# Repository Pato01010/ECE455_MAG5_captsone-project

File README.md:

# AfriCAN DETECT IT: Proton-Precession Magnetometer

This project is a towed underwater magnetometer for marine magnetic surveying and object recovery. It's dragged behind a boat and maps small changes in Earth's magnetic field, the kind made by shipwrecks, debris, and other metal objects on or under the seafloor.

The goal is a low-cost instrument with **sub-1 nT sensitivity**, every reading tagged with **GPS position**, and everything packed into a **waterproof towfish** that works in the field.

## How it works

The system is a proton-precession magnetometer (PPM). A coil is wrapped around a container of hydrogen-rich fluid, such as water or kerosene.

1. **Polarize.** A large DC current through the coil sets up a strong field that lines up the proton spins in the fluid.
2. **Release.** The current is cut quickly. The protons start to precess around Earth's field.
3. **Sense.** The precessing protons induce a weak signal in the same coil, in the microvolt range and decaying over a few seconds.
4. **Measure.** The precession frequency is directly proportional to field strength (about 42.58 Hz per µT, which is roughly 2 kHz in Earth's field). Counting that frequency precisely gives an absolute field reading.
5. **Log.** Each reading is timestamped and paired with a GPS fix, so a survey becomes a map of the magnetic field.

The method is attractive because the measurement comes from a physical constant, the proton's gyromagnetic ratio. It doesn't drift and needs no calibration. The hard part is pulling a tiny, decaying signal out of noise right after a high-current pulse.

## System design

```
 ┌────────────┐   ┌──────────┐   ┌──────────────┐   ┌──────────────┐   ┌─────────┐
 │Polarization│──▶│ Sensor   │──▶│ Blanking +   │──▶│ Filtering &  │──▶│   MCU   │
 │  driver    │   │  coil    │   │   preamp     │   │    gain      │   │ freq.   │
 └────────────┘   └──────────┘   └──────────────┘   └──────────────┘   │ counter │
                                                                       └────┬────┘
                                                          GPS ─────────────▶│
                                                                            ▼
                                                                    Logged survey data
```

| Subsystem                       | Role                                                                                                                   |
| ------------------------------- | ---------------------------------------------------------------------------------------------------------------------- |
| **Polarization driver**   | Switches high current into the coil, then shuts it off fast and cleanly                                                |
| **Sensor coil**           | Polarizes the fluid, then picks up the precession signal                                                               |
| **Blanking + preamp**     | Shields the sensitive front end during turn-off, then amplifies the weak signal with as little added noise as possible |
| **Signal conditioning**   | Band-pass filtering and gain centered on the expected precession frequency                                             |
| **Frequency measurement** | MCU-based period counting for precise frequency estimates over a short, decaying signal                                |
| **GPS integration**       | Position and timing for every reading                                                                                  |
| **Isolation**             | Keeps switching noise and ground currents from the power side out of the analog chain                                  |
| **Towfish housing**       | Waterproof, non-magnetic enclosure that keeps the sensor stable and away from the boat's own magnetic signature        |

## Our approach

We're building this as a set of independent subsystems. Each one is designed, built, and tested on its own before integration. That lets us confirm each stage works and track down problems without guessing which part of the chain is at fault.

**1. Design for the signal.** The precession signal is tiny and short-lived, so every design choice starts from the noise budget: coil geometry and wire, preamp noise, filter bandwidth, and how fast the front end can recover after the polarizing pulse.

**2. Prototype and test on the bench.** Each subsystem gets its own custom PCB and bench test. We check polarization switching, front-end blanking and gain, coil pickup, and frequency and GPS logging separately against known inputs.

**3. Fight noise and ringing.** The biggest challenges are coil ringing after turn-off, environmental and switching noise, and weak-signal recovery. We handle these with fast, well-damped switching, careful blanking, narrow filtering, shielding, and isolating the high-current side from the analog side.

**4. Integrate in stages.** Subsystems are combined one at a time, and we confirm performance at each step before adding the next.

**5. Package and field test.** The finished electronics go into the towfish. We test it in the water, first over open water and then over known magnetic targets, to verify sensitivity and positioning in real survey conditions.

## Repo layout

```
hardware/     Schematics and PCB layouts for each subsystem
firmware/     MCU code for timing, frequency measurement, and GPS logging
analysis/     Scripts for processing survey data and making field maps
mechanical/   Towfish housing design files
docs/         Design notes, test results, and bring-up procedures
```

## Safety

The polarization stage switches high current into an inductive load. Read the bring-up notes in `docs/` before powering the hardware, and confirm the blanking and flyback paths are in place first.

## Team

**AfriCAN DETECT IT**, Electrical & Computer Engineering, University of Wisconsin–Madison.

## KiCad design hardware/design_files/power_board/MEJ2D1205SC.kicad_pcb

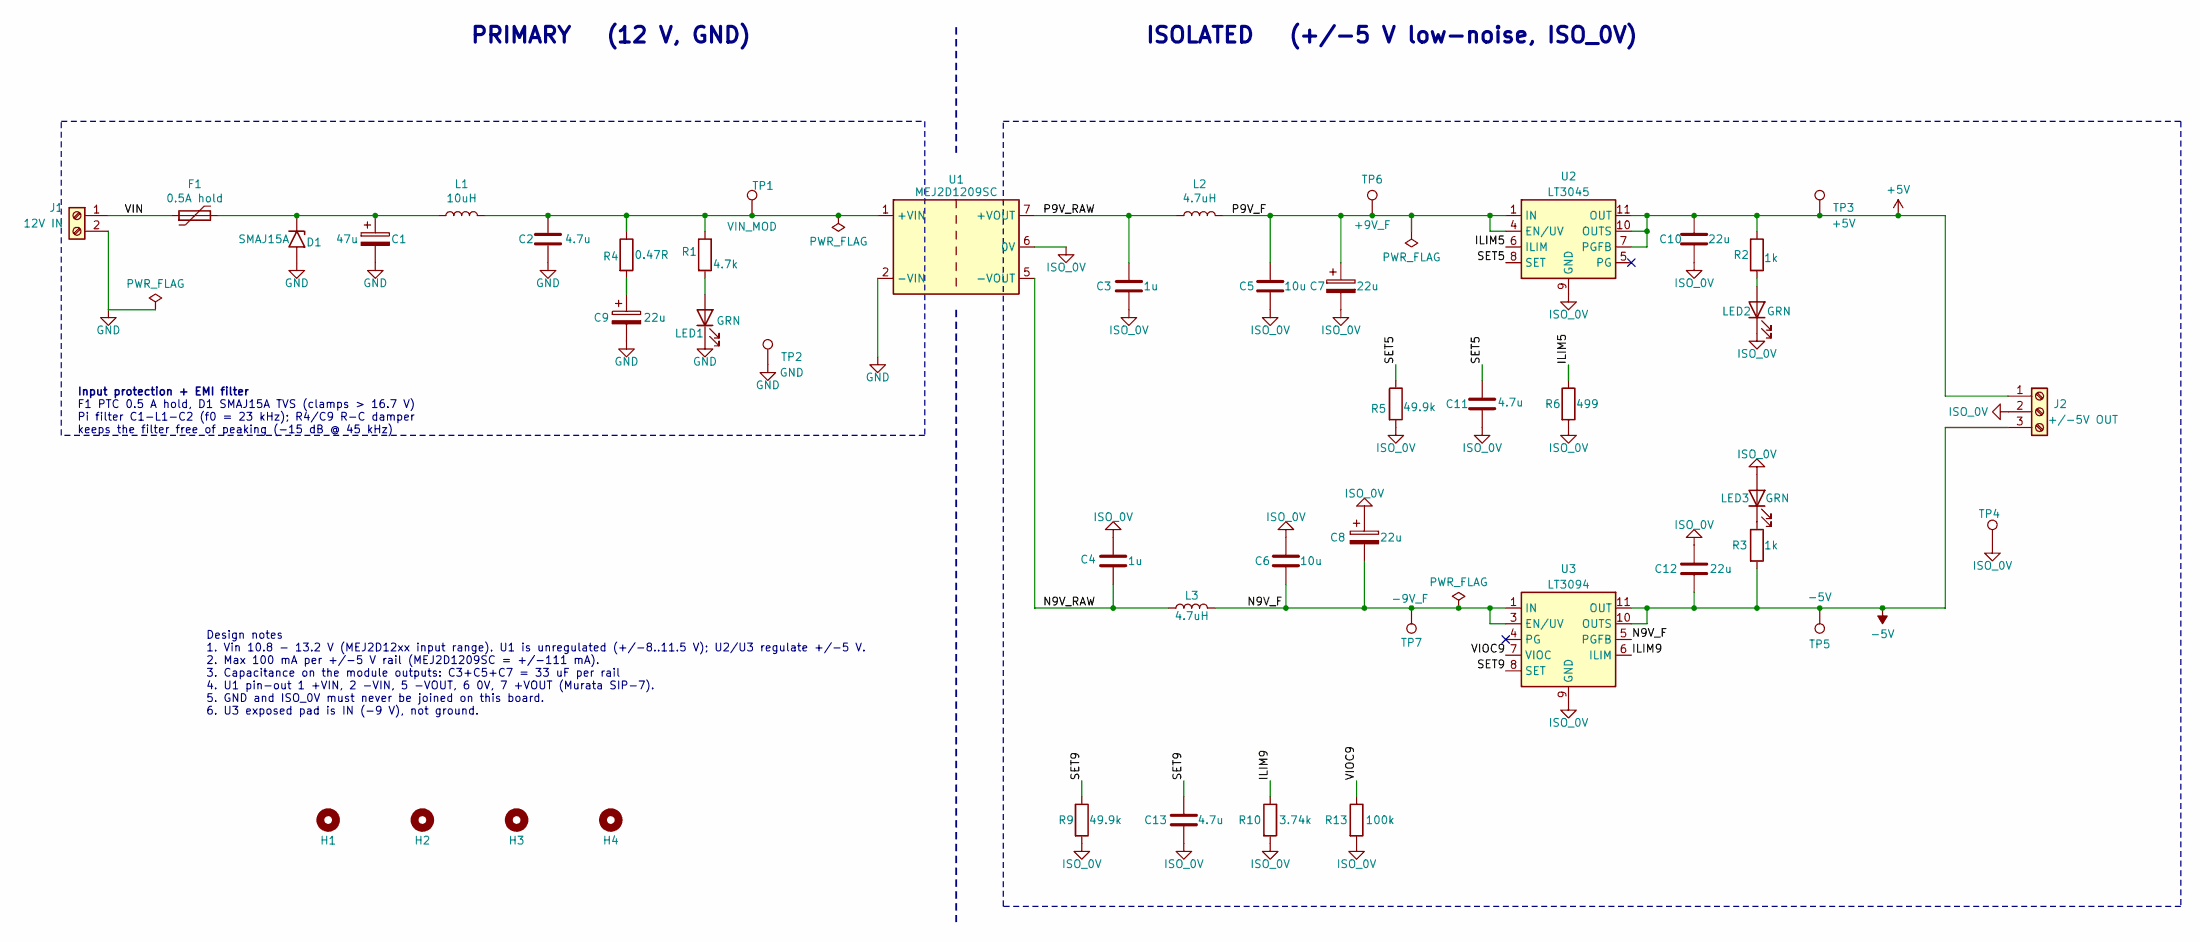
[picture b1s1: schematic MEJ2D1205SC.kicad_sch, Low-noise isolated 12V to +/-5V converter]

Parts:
C1: 47u; CP_Elec_6.3x7.7; MPN Panasonic EEE-FK1E470P
C2: 4.7u; C_1206_3216Metric; MPN Murata GRM31CR71E475KA88
C3, C4: 1u; C_0805_2012Metric; MPN Murata GRM21BR71C105KA01L
C5, C6: 10u; C_1206_3216Metric; MPN Murata GRM31CR71E106KA12L
C7, C8, C9: 22u; CP_Elec_5x5.8; MPN Panasonic EEE-FK1E220R
C10, C12: 22u; C_1210_3225Metric; MPN Murata GRM32ER71C226KE18L
C11, C13: 4.7u; C_1206_3216Metric; MPN Murata GRM31CR71C475KA01L
D1: SMAJ15A; D_SMA; MPN Littelfuse SMAJ15A
F1: 0.5A hold; Fuse_1206_3216Metric; MPN Littelfuse 1206L050/15YR
H1, H2, H3, H4: M3; MountingHole_3.2mm_M3
J1: 12V IN; TerminalBlock_Phoenix_MKDS-1,5-2-5.08_1x02_P5.08mm_Horizont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; MPN Phoenix Contact 1729128
J2: +/-5V OUT; TerminalBlock_Phoenix_MKDS-1,5-3-5.08_1x03_P5.08mm_Horizont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; MPN Phoenix Contact 1729131
L1: 10uH; L_Bourns-SRN4018; MPN Bourns SRN4018-100M
L2, L3: 4.7uH; L_Bourns-SRN4018; MPN Bourns SRN4018-4R7M
LED1, LED2, LED3: GRN; LED_0805_2012Metric; MPN Lite-On LTST-C171GKT
R1: 4.7k; R_0805_2012Metric; MPN Yageo RC0805FR-074K7L
R2, R3: 1k; R_0805_2012Metric; MPN Yageo RC0805FR-071KL
R4: 0.47R; R_0805_2012Metric; MPN Yageo RL0805FR-070R47L
R5, R9: 49.9k; R_0805_2012Metric; MPN Panasonic ERA-6AEB4992V
R6: 499; R_0805_2012Metric; MPN Yageo RC0805FR-07499RL
R10: 3.74k; R_0805_2012Metric; MPN Yageo RC0805FR-073K74L
R13: 100k; R_0805_2012Metric; MPN Yageo RC0805FR-07100KL
TP1: VIN_MOD; TestPoint_Keystone_5010-5014_Multipurpose; MPN Keystone 5010
TP2: GND; TestPoint_Keystone_5010-5014_Multipurpose; MPN Keystone 5011
TP3: +5V; TestPoint_Keystone_5010-5014_Multipurpose; MPN Keystone 5010
TP4: ISO_0V; TestPoint_Keystone_5010-5014_Multipurpose; MPN Keystone 5011
TP5: -5V; TestPoint_Keystone_5010-5014_Multipurpose; MPN Keystone 5010
TP6: +9V_F; TestPoint_Keystone_5010-5014_Multipurpose; MPN Keystone 5010
TP7: -9V_F; TestPoint_Keystone_5010-5014_Multipurpose; MPN Keystone 5010
U1: MEJ2D1209SC; Murata_MEJ2DxxxxSC_THT; MPN Murata MEJ2D1209SC
U2: LT3045; MSOP-12-1EP_3x4.039mm_P0.65mm_EP1.651x2.845mm; MPN Analog Devices LT3045EMSE#PBF
U3: LT3094; MSOP-12-1EP_3x4.039mm_P0.65mm_EP1.651x2.845mm; MPN Analog Devices LT3094EMSE#PBF

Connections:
+5V: C10.1, J2.1, R2.1, TP3.1 (1_1), U2.7 (PGFB), U2.10 (OUTS), U2.11 (OUT), U2.12 (OUT)
-5V: C12.2, J2.3, R3.2, TP5.1 (1_1), U3.10 (OUTS), U3.11 (OUT), U3.12 (OUT)
/ILIM5: R6.1, U2.6 (ILIM)
/ILIM9: R10.1, U3.6 (ILIM)
/N9V_F: C6.2, C8.2, L3.2, TP7.1 (1_1), U3.1 (IN), U3.2 (IN), U3.3 (EN/UV), U3.5 (PGFB), U3.13 (IN)
/N9V_RAW: C4.2, L3.1, U1.5 (-VOUT)
/P9V_F: C5.1, C7.1, L2.2, TP6.1 (1_1), U2.1 (IN), U2.2 (IN), U2.3 (IN), U2.4 (EN/UV)
/P9V_RAW: C3.1, L2.1, U1.7 (+VOUT)
/SET5: C11.1, R5.1, U2.8 (SET)
/SET9: C13.1, R9.1, U3.8 (SET)
/VIN: F1.1, J1.1
/VIOC9: R13.1, U3.7 (VIOC)
GND: C1.2, C2.2, C9.2, D1.2 (A), J1.2, LED1.1 (K), TP2.1 (1_1), U1.2 (-VIN)
ISO_0V: C3.2, C4.1, C5.2, C6.1, C7.2, C8.1, C10.2, C11.2, C12.1, C13.2, J2.2, LED2.1 (K), LED3.2 (A), R5.2, R6.2, R9.2, R10.2, R13.2, TP4.1 (1_1), U1.6 (0V), U2.9 (GND), U2.13 (GND), U3.9 (GND)
unnamed: C9.1, R4.2
unnamed: C1.1, D1.1 (K), F1.2, L1.1
unnamed: LED1.2 (A), R1.2
unnamed: LED2.2 (A), R2.2
unnamed: LED3.1 (K), R3.1
unnamed: C2.1, L1.2, R1.1, R4.1, TP1.1 (1_1), U1.1 (+VIN)

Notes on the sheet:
ISOLATED (+/-5 V low-noise, ISO_0V)
Design notes 1. Vin 10.8 - 13.2 V (MEJ2D12xx input range). U1 is unregulated (+/-8..11.5 V); U2/U3 regulate +/-5 V. 2. Max 100 mA per +/-5 V rail (MEJ2D1209SC = +/-111 mA). 3. Capacitance on the module outputs: C3+C5+C7 = 33 uF per rail 4. U1 pin-out 1 +VIN, 2 -VIN, 5 -VOUT, 6 0V, 7 +VOUT (Murata S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
F1 PTC 0.5 A hold, D1 SMAJ15A TVS (clamps > 16.7 V) Pi filter C1-L1-C2 (f0 = 23 kHz); R4/C9 R-C damper keeps the filter free of peaking (-15 dB @ 45 kHz)
PRIMARY (12 V, GND)
Input protection + EMI filter

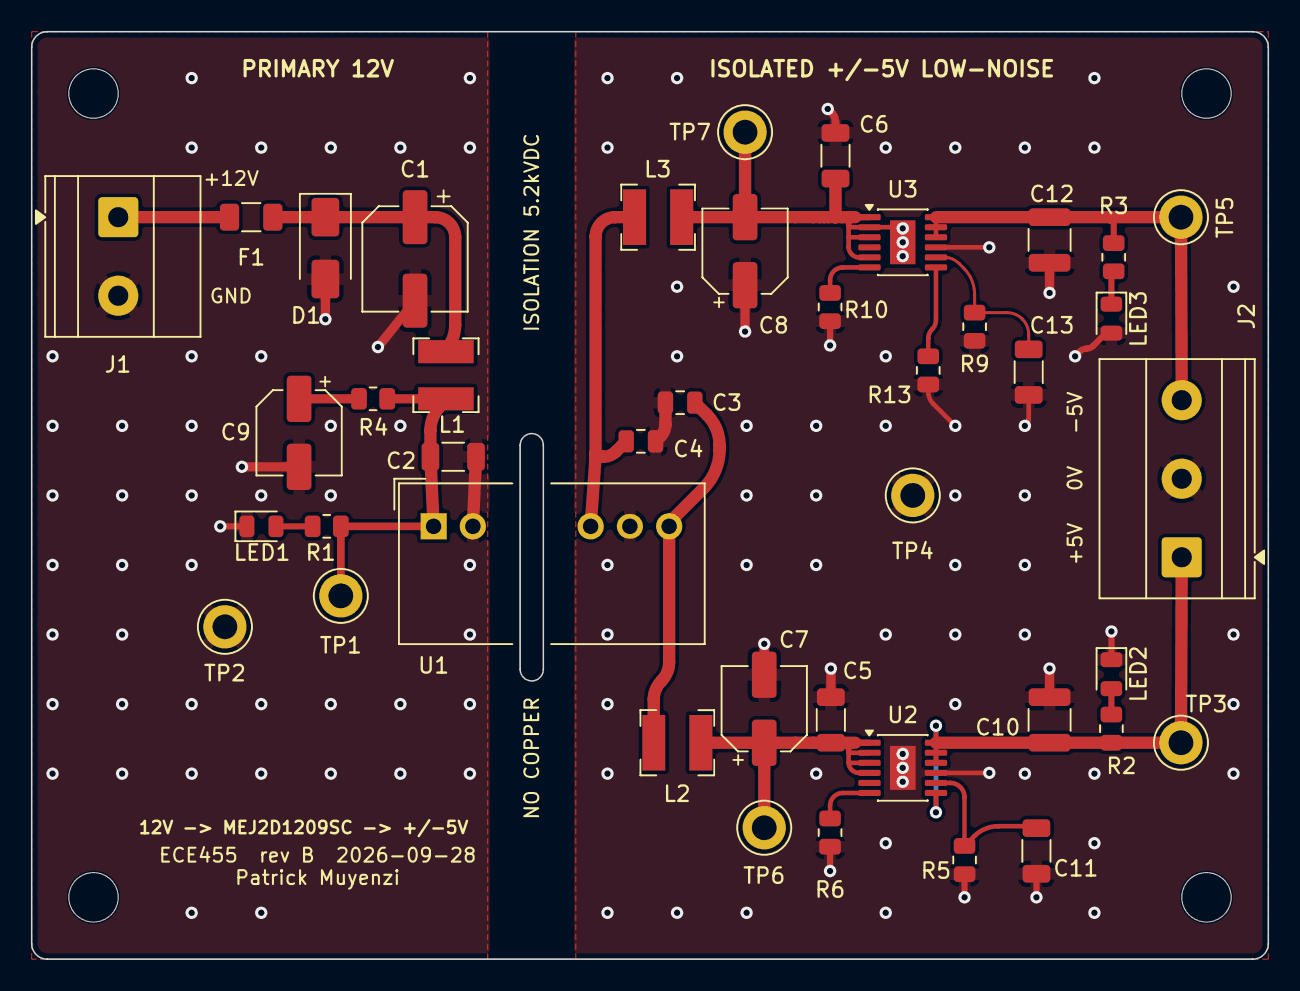
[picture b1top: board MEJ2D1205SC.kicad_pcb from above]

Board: 2 copper layers, 80.0 x 60.0 mm, 46 parts (0 on the bottom side), 20 nets.

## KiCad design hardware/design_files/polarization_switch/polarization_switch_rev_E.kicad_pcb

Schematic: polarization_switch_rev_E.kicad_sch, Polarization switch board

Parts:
C1: 470u/25V; CP_Elec_10x10.5
C2, C7: 1n/630V; C_1206_3216Metric_Pad1.33x1.80mm_HandSolder
C3: 10n C0G; C_1206_3216Metric_Pad1.33x1.80mm_HandSolder
C4: 2.2u/50V; C_1206_3216Metric_Pad1.33x1.80mm_HandSolder
C5, C6: 100n; C_1206_3216Metric_Pad1.33x1.80mm_HandSolder
C8: 10u; C_1206_3216Metric_Pad1.33x1.80mm_HandSolder
D1, D5: MURS360; D_SMC_Handsoldering
D2, D4: 1N4148W; D_SOD-123
D3: 1.5SMC200A; D_SMC_Handsoldering
F1: 2A T; Fuseholder_Littelfuse_Nano2_157x
F2: 125mA F; Fuse_1206_3216Metric_Pad1.42x1.75mm_HandSolder
H1, H2, H3, H4: M3; MountingHole_3.2mm_M3
J1: 2x10 stack; PinSocket_2x10_P2.54mm_Vertical
J2: COIL; TerminalBlock_Phoenix_MKDS-1,5-2-5.08_1x02_P5.08mm_Horizont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
J3: 12V IN; TerminalBlock_Phoenix_MKDS-1,5-2-5.08_1x02_P5.08mm_Horizont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
J4: GATE LINK; PinHeader_1x02_P2.54mm_Vertical
K1: G6S-2F DC12; Relay_DPDT_Omron_G6S-2F
Q1: MMBT3904; SOT-23
Q2: R6020KNJ; TO-263-2
R1: R_LIM; R_Axial_Power_L48.0mm_W12.5mm_P60.96mm; not fitted
R2, R5, R7: 10k; R_1206_3216Metric_Pad1.30x1.75mm_HandSolder
R3: 2.2k; R_1206_3216Metric_Pad1.30x1.75mm_HandSolder
R4: 10k; R_2512_6332Metric_Pad1.40x3.35mm_HandSolder
R6: 47; R_1206_3216Metric_Pad1.30x1.75mm_HandSolder
R8: 1k; R_1206_3216Metric_Pad1.30x1.75mm_HandSolder
R9: 20m; R_Shunt_Ohmite_LVK12
R10: 22k; R_2512_6332Metric_Pad1.40x3.35mm_HandSolder
R11: 1M; R_1206_3216Metric_Pad1.30x1.75mm_HandSolder
R12: 18; R_1206_3216Metric_Pad1.30x1.75mm_HandSolder
TP1: GATE; TestPoint_Keystone_5015_Micro_Mini
TP2: DRAIN; TestPoint_Keystone_5015_Micro_Mini
TP3: SRC; TestPoint_Keystone_5015_Micro_Mini
TP4: I_SENSE; TestPoint_Keystone_5015_Micro_Mini
U1: MCP1407-E/SN; SOIC-8_3.9x4.9mm_P1.27mm
U2: INA180A2; SOT-23-5

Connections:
+3V3A: C5.1, J1.20, U2.5 (V+)
+12V: C1.1, C4.1, C6.1, D2.1 (K), D4.1 (K), J1.1, J1.3, J3.1, K1.1, K1.4, K1.9, R11.1, U1.1 (VDD), U1.8 (VDD)
/CMD_GATE: J1.17, R2.1, U1.2 (INPUT)
/CMD_RLY: J1.18, R3.1
/COIL_N: C7.2, D5.2 (A), J2.2, R10.2
/COIL_P: C7.1, D1.1 (K), D4.2 (A), F1.2, J2.1, R1.2, R10.1
/DRAIN: D3.1 (K), D5.1 (K), Q2.2 (D), R4.1, R11.2, TP2.1
/ISNS_N: R9.3, U2.4 (-)
/ISNS_P: R9.2, U2.3 (+)
/I_SENSE_TLMRY: C3.1, J1.11, R8.2, TP4.1
/SNUB: C2.1, R4.2
/V12_SW: F1.1, K1.5, K1.8, R1.1
/XFER: J1.13, R12.2
GND: C1.2, C2.2, C3.2, C4.2, C5.2, C6.2, C8.2, D1.2 (A), D3.2 (A), J1.2, J1.4, J1.12, J3.2, Q1.2 (E), R2.2, R5.2, R9.4, U1.4 (GND), U1.5 (GND), U2.2 (GND)
unnamed: D2.2 (A), K1.12, Q1.3 (C)
unnamed: F2.1, R12.1
unnamed: F2.2, K1.3, K1.10
unnamed: J4.1, U1.6 (OUTPUT), U1.7 (OUTPUT)
unnamed: J4.2, R6.1
unnamed: C8.1, Q1.1 (B), R3.2, R5.1
unnamed: Q2.1 (G), R6.2, R7.1, TP1.1
unnamed: Q2.3 (S), R7.2, R9.1, TP3.1
unnamed: R8.1, U2.1

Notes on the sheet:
RELAY (K1) DRIVER
POLARIZATION COIL VALUES ARE ESTIMATED
BLOCKING DIODE & DAMPING
CURRENT SENSE
CMD_RLY (bus RLY_CMD) high: K_XFER releases; K1 makes ~7 ms later (R3/C8 delay). CMD_GATE >= 30 ms later, on 2-4 s. Gate off; CMD_RLY low at +0.5 ms. K1 opens at ~+3.5 ms, its NC feeds XFER and the front end transfers the coil (~+12 ms). TUNE (+5 ms), BLANK2 (+45 ms) and the record (+60 ms) are fro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
Blocking Diodes tested and verified on PCB
GATE DRIVE
K1's NC contacts (pins 3 and 10) feed bus pin 13 (XFER, cut from GND on all four boards) through F2 (125 mA) and R12 (18 ohm) while K1 is released: ~12 V, 11-13 mA to K_XFER. F2 opens within milliseconds if pin 13 is ever left on GND. It does NOT protect 3V3D, I_SENSE or TUNE: continuity-check pins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
COIL FEED & FUSE
POLARIZATION SWITCH BOARD
REV B ADDITIONS: D4, D5, C7, R10, R11
DECOUPLING
BUS, 12 V INPUT & BULK CAP
Relay Driver tested and verified on PCB
ERC POWER FLAGS
D5 blocks the post-clamp reverse current; C7 + R10 make the swing through zero fast and damp it (C7 1 nF for up to 15 m of Belden-8760-class head cable; longer or higher-capacitance cable must be re-simulated); R11 bleeds DRAIN to +12V between shots; D4 clamps any open in the COIL_P feed.
COIL
Gate driver, MOSFET and Clamp tested and verified on PCB
REV C ADDITIONS: R12, XFER (bus pin 13)
REV E (2026-10-14): THE 80 x 60 STACK
REV D ADDITIONS (2026-10-13): SMD PARTS, 1206 MINIMUM
POWER SWITCH & CLAMP
Patrick Muyenzi's power board (isolated +/-5 V) replaces the rev C power board. This board takes its outline: 80 x 60 mm, M3 holes 4 mm in from each edge. Circuit = rev D plus J3, the 12 V input (Phoenix MKDS 1,5/2-5,08, beside Patrick's J1). The bus moved to x 62 mm; pins 1/3 carry 12 V up to the 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
XFER
K1 is an Omron G6S-2F (SMD, both poles in parallel); R3/C8 delay its make so K_XFER is back on NC first (interlock margin 6.1 ms, simulated). F1, an on-board NANO2 2 A slow-blow fuse in a clip, replaces J3 and the in-line fuse. F2 + R12 replace the fusible NFR25. R9 is a four-terminal Kelvin shunt 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
SEQUENCE (fixed delays, never timed on I_SENSE)
DRAIN reaches ~222 V at switch-off and COIL_N swings from +223 V to -154 V (D5 holds up to ~347 V between them). DRAIN, COIL_N and SNUB are in net class HV; keep XFER >= 1.25 mm from all three.
MOUNTING HOLES
NOTES
HIGH VOLTAGE
Rev C coil, COMPUTED, PROVISIONAL: 690 t of 22 AWG as two counter-wound 345 t halves in series (2.75 in acrylic tubes, water in both): ~11.3 mH, 8.3 ohm (9.6 hot), C_p 0.14-0.59 nF, ~4.0 mT/A. From 12 V: ~1.3 A cold / 1.1 A hot (1.19 / 1.03 A through 15 m of head cable).

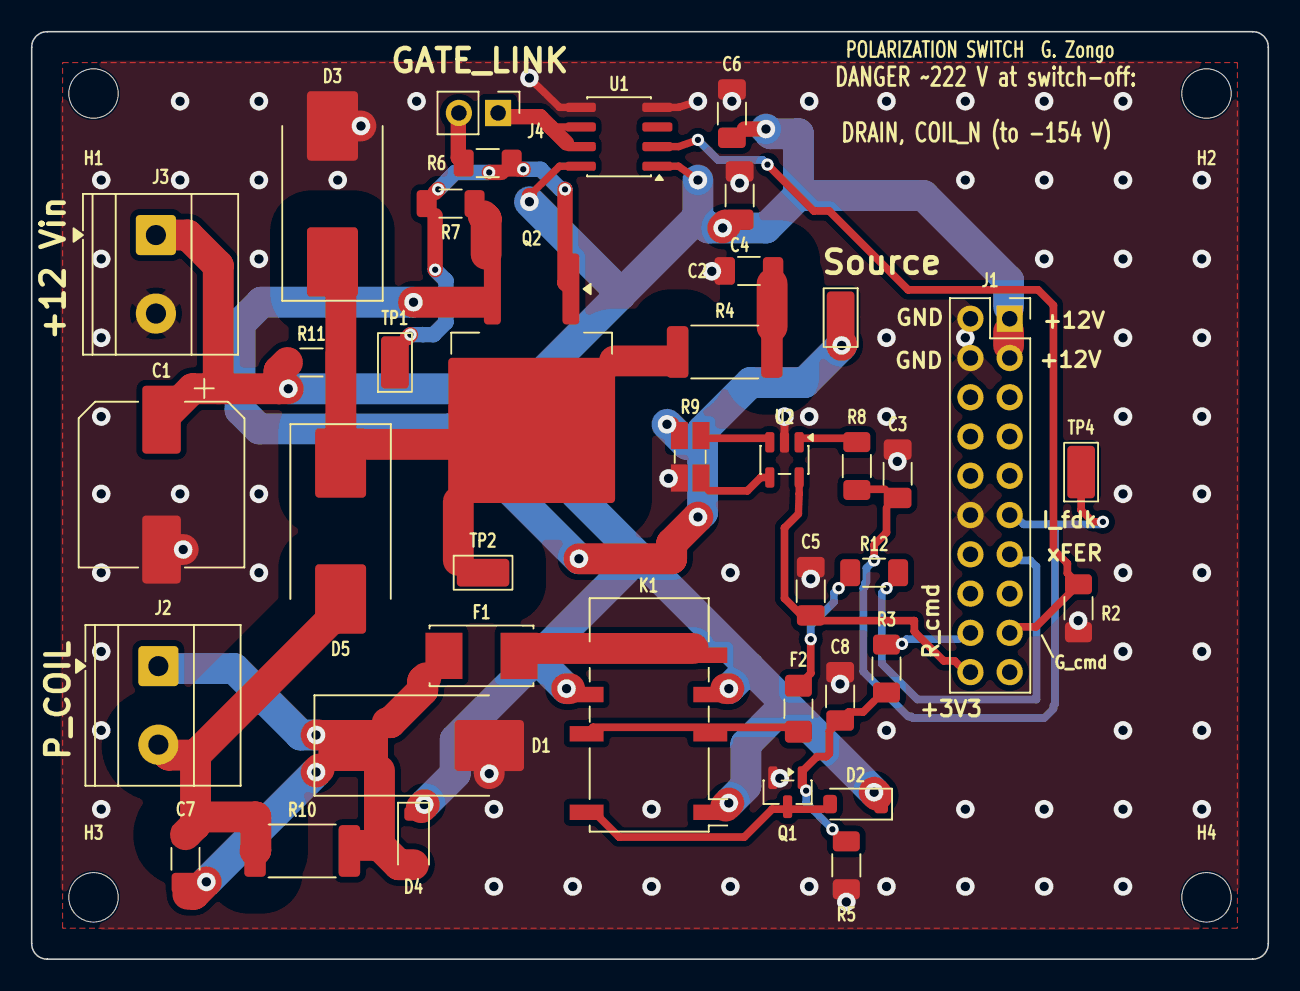
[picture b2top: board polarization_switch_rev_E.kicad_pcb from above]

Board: 2 copper layers, 80.0 x 60.0 mm, 43 parts (0 on the bottom side), 23 nets.

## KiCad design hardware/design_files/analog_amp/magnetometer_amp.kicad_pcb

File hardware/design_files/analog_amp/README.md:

# Analog Amplifier — Proton-Precession Magnetometer (ECE 455)

## Purpose
The analog amplifier conditions the weak precession signal from the sensing coil for downstream frequency measurement. The design targets a signal near 2.4 kHz and interfaces with a 0–3.3 V ADC.

## Architecture
- Sensing-coil/tank input (`TANK`).
- OPA4227 quad op-amp signal conditioning, including preamplification, filtering and additional gain.
- Nominal first-stage non-inverting gain: `1 + 100 kΩ / 1 kΩ = 101 V/V` (not measured system gain).
- ±5 V analog supply and 3.3 V reference input.
- 10 kΩ / 10 kΩ divider nominally generating 1.65 V `VMID`; separate buffered bias output for ADC level shifting.

## Folder guide
- `kicad/`: editable PCB, schematic and project configuration from supplied uploads.
- `bom/placement_bom.csv`: one row per footprint extracted from PCB.
- `bom/grouped_bom.csv`: grouped BOM; manufacturer and supplier part numbers require confirmation.
- `docs/`: hardware test log and manufacturing instructions.
- `manufacturing/gerbers/`: **no Gerbers included**; export from verified PCB in KiCad.
- `mechanical/stl/`: **no STL included**; no matching 3D CAD source supplied.

## Prototype status (2026-10-30)
PCB assembled and bench-tested with laboratory supply, oscilloscope, multimeter and function generator. ±5 V and 3.3 V supply readings were subsequently reported correct. Reference-node measurements have been inconsistent (nominal VMID +1.65 V; previous readings include about +1.78 V and −2.23 V), and require repeatable probing against PCB ground. End-to-end gain and frequency response have not been validated.

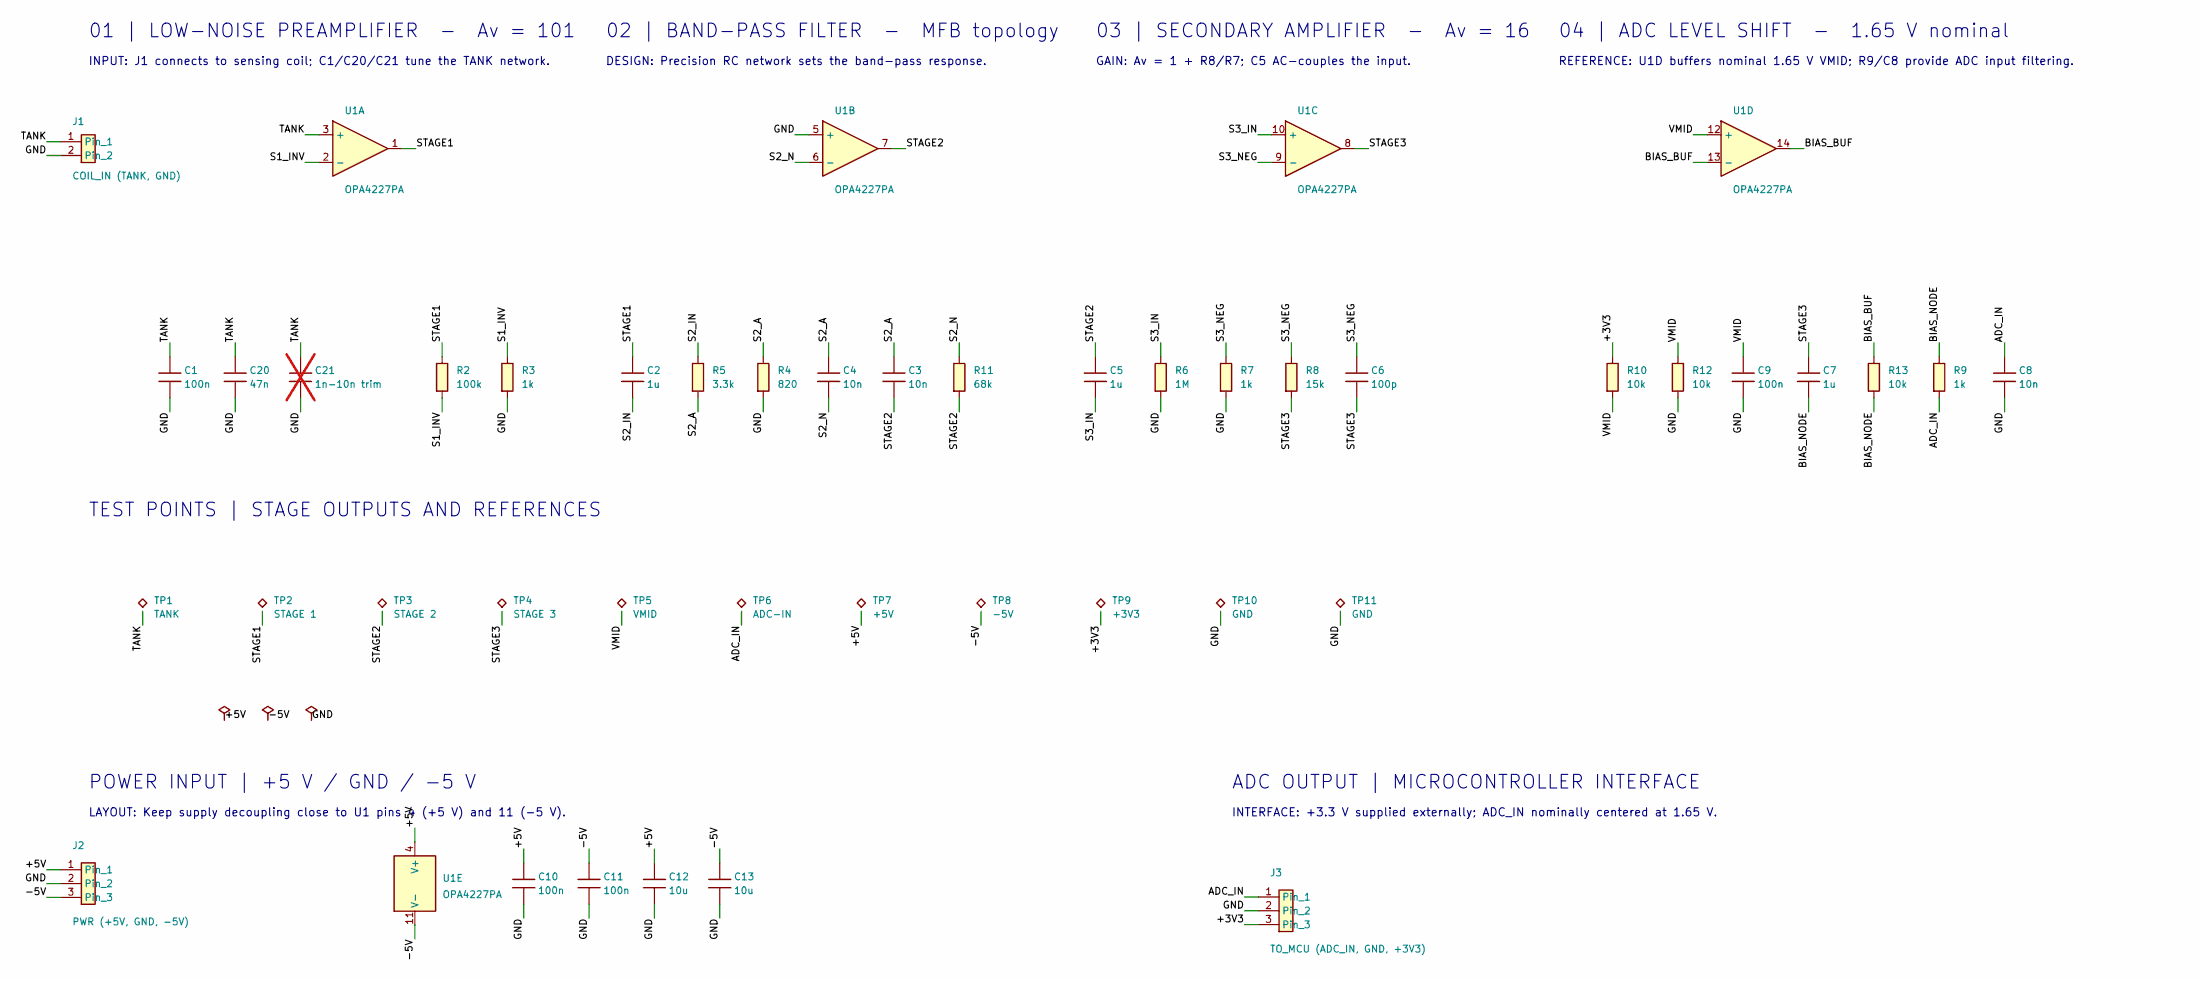
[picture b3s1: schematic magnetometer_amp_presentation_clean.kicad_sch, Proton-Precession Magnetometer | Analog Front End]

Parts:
C1: 100n; C1_Film_ECH_U1C104JX5; MPN ECH-U1C104JX5
C2: 1u; C2_Film_SMDIC04100TB00KQ00; MPN SMDIC04100TB00KQ00
C3: 10n; C3_Film_ECH_U1H103GX5; MPN ECH-U1H103GX5
C4: 10n; C4_Film_ECH_U1H103GX5; MPN ECH-U1H103GX5
C5: 1u; C5_Film_SMDIC04100TB00KQ00; MPN SMDIC04100TB00KQ00
C6: 100p; C6_C_0603_1608Metric
C7: 1u; C7_Film_SMDIC04100TB00KQ00; MPN SMDIC04100TB00KQ00
C8: 10n; C8_Film_ECH_U1H103GX5; MPN ECH-U1H103GX5
C9: 100n; C9_C_0603_1608Metric
C10: 100n; C10_C_0603_1608Metric
C11: 100n; C11_C_0603_1608Metric
C12: 10u; C12_C_1206_3216Metric
C13: 10u; C13_C_1206_3216Metric
C20: 47n; C20_Film_ECH_U1H473JX9; MPN ECH-U1H473JX9
C21: 1n-10n trim; C21_C_0805_2012Metric; not fitted
J1: COIL_IN (TANK, GND); J1_PinHeader_1x02_P2.54mm_Vertical
J2: PWR (+5V, GND, -5V); J2_PinHeader_1x03_P2.54mm_Vertical
J3: TO_MCU (ADC_IN, GND, +3V3); J3_PinHeader_1x03_P2.54mm_Vertical
R2: 100k; R2_R_0603_1608Metric
R3: 1k; R3_R_0603_1608Metric
R4: 820; R4_R_0603_1608Metric
R5: 3.3k; R5_R_0603_1608Metric
R6: 1M; R6_R_0603_1608Metric
R7: 1k; R7_R_0603_1608Metric
R8: 15k; R8_R_0603_1608Metric
R9: 1k; R9_R_0603_1608Metric
R10: 10k; R10_R_0603_1608Metric
R11: 68k; R11_R_0603_1608Metric
R12: 10k; R12_R_0603_1608Metric
R13: 10k; R13_R_0603_1608Metric
TP1: TANK; TP1_TestPoint_Loop_D2.50mm_Drill1.0mm
TP2: STAGE 1; TP2_TestPoint_Loop_D2.50mm_Drill1.0mm
TP3: STAGE 2; TP3_TestPoint_Loop_D2.50mm_Drill1.0mm
TP4: STAGE 3; TP4_TestPoint_Loop_D2.50mm_Drill1.0mm
TP5: VMID; TP5_TestPoint_Loop_D2.50mm_Drill1.0mm
TP6: ADC-IN; TP6_TestPoint_Loop_D2.50mm_Drill1.0mm
TP7: +5V; TP7_TestPoint_Loop_D2.50mm_Drill1.0mm
TP8: -5V; TP8_TestPoint_Loop_D2.50mm_Drill1.0mm
TP9: +3V3; TP9_TestPoint_Loop_D2.50mm_Drill1.0mm
TP10: GND; TP10_TestPoint_Loop_D2.50mm_Drill1.0mm
TP11: GND; TP11_TestPoint_Loop_D2.50mm_Drill1.0mm
U1: OPA4227PA; U1_DIP-14_W7.62mm

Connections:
/+3V3: J3.3, R10.1, TP9.1
/+5V: C10.1, C12.1, J2.1, TP7.1, U1.4 (V+)
/-5V: C11.1, C13.1, J2.3, TP8.1, U1.11 (V-)
/ADC_IN: C8.1, J3.1, R9.2, TP6.1
/BIAS_BUF: R13.1, U1.13 (-), U1.14
/BIAS_NODE: C7.2, R9.1, R13.2
/GND: C1.2, C8.2, C9.2, C10.2, C11.2, C12.2, C13.2, C20.2, C21.2, J1.2, J2.2, J3.2, R3.2, R4.2, R6.2, R7.2, R12.2, TP10.1, TP11.1, U1.5 (+)
/S1_INV: R2.2, R3.1, U1.2 (-)
/S2_A: C3.1, C4.1, R4.1, R5.2
/S2_IN: C2.2, R5.1
/S2_N: C4.2, R11.1, U1.6 (-)
/S3_IN: C5.2, R6.1, U1.10 (+)
/S3_NEG: C6.1, R7.1, R8.1, U1.9 (-)
/STAGE1: C2.1, R2.1, TP2.1, U1.1
/STAGE2: C3.2, C5.1, R11.2, TP3.1, U1.7
/STAGE3: C6.2, C7.1, R8.2, TP4.1, U1.8
/TANK: C1.1, C20.1, C21.1, J1.1, TP1.1, U1.3 (+)
/VMID: C9.1, R10.2, R12.1, TP5.1, U1.12 (+)

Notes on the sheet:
REFERENCE: U1D buffers nominal 1.65 V VMID; R9/C8 provide ADC input filtering.
LAYOUT: Keep supply decoupling close to U1 pins 4 (+5 V) and 11 (-5 V).
INTERFACE: +3.3 V supplied externally; ADC_IN nominally centered at 1.65 V.
02 | BAND-PASS FILTER - MFB topology
04 | ADC LEVEL SHIFT - 1.65 V nominal
INPUT: J1 connects to sensing coil; C1/C20/C21 tune the TANK network.
GAIN: Av = 1 + R8/R7; C5 AC-couples the input.
01 | LOW-NOISE PREAMPLIFIER - Av = 101
03 | SECONDARY AMPLIFIER - Av = 16
DESIGN: Precision RC network sets the band-pass response.
TEST POINTS | STAGE OUTPUTS AND REFERENCES
POWER INPUT | +5 V / GND / -5 V
ADC OUTPUT | MICROCONTROLLER INTERFACE

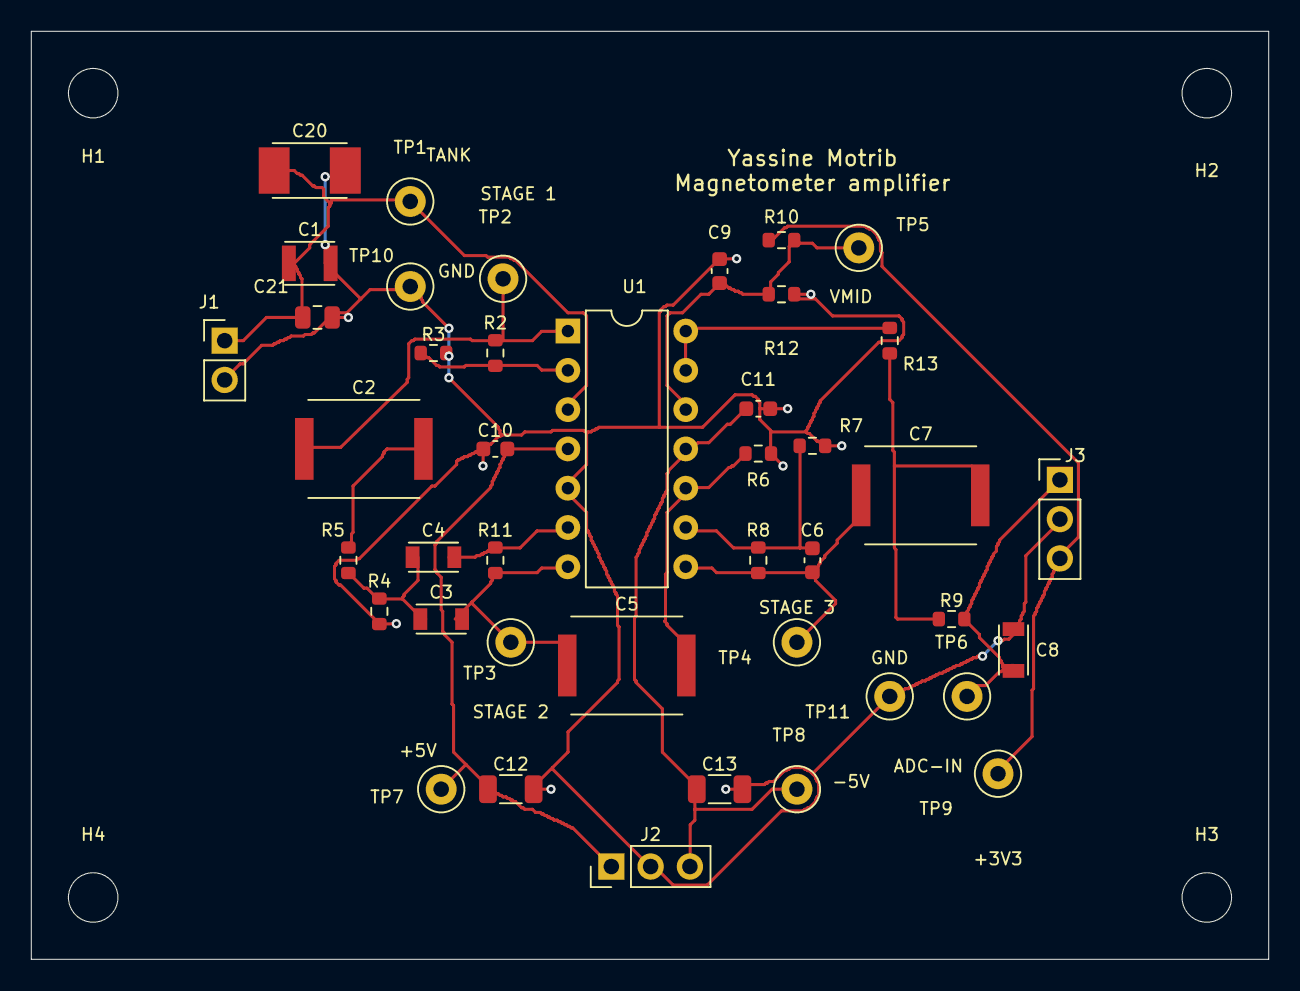
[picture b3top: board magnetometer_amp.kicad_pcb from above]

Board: 2 copper layers, 80.0 x 60.0 mm, 46 parts (0 on the bottom side), 18 nets.

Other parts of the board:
H1: H1_MountingHole_3.2mm_M3
H2: H2_MountingHole_3.2mm_M3
H3: H3_MountingHole_3.2mm_M3
H4: H4_MountingHole_3.2mm_M3
